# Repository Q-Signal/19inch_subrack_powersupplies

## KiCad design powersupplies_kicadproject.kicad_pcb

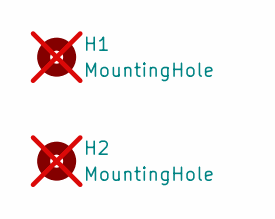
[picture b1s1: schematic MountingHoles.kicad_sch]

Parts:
H1, H2: MountingHole; MountingHole_2.7mm_M2.5; not fitted

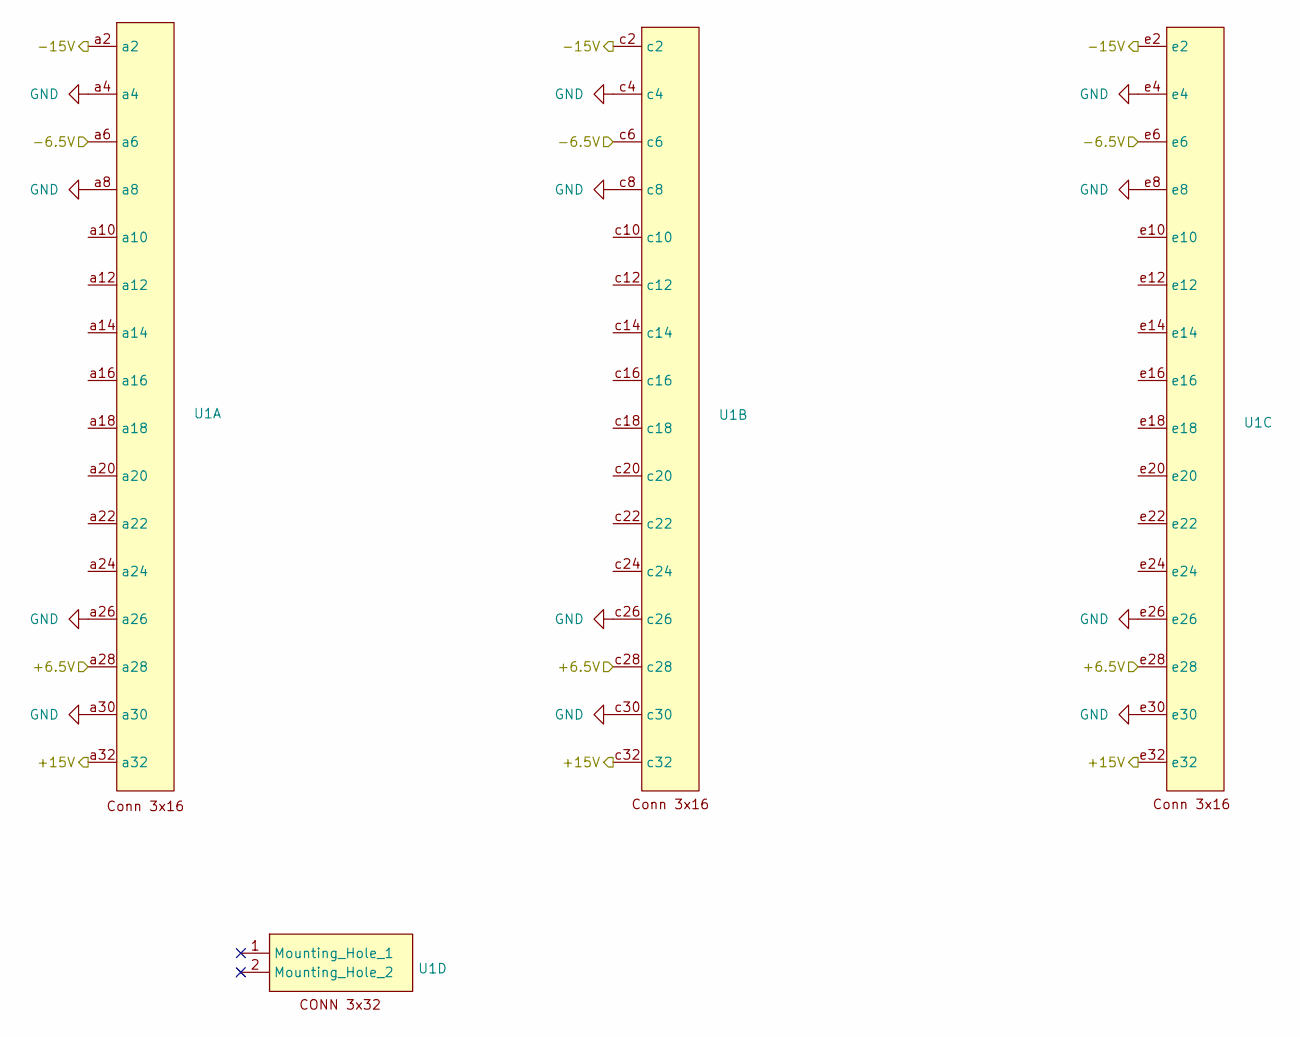
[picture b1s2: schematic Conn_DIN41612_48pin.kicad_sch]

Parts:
U1: DIN41612_ace_3x16_RA_Male; Manufacturer Part Number 09051486931; DigiKey Part Number 1195-1240-ND

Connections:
/6.5V Dual Rail Power/+6.5V: U1.a28, U1.c28, U1.e28; also elsewhere on the board
/6.5V Dual Rail Power/+15V: U1.a32, U1.c32, U1.e32; also elsewhere on the board
/6.5V Dual Rail Power/-6.5V: U1.a6, U1.c6, U1.e6; also elsewhere on the board
/6.5V Dual Rail Power/-15V: U1.a2, U1.c2, U1.e2; also elsewhere on the board
GND: U1.a4, U1.a8, U1.a26, U1.a30, U1.c4, U1.c8, U1.c26, U1.c30, U1.e4, U1.e8, U1.e26, U1.e30; also elsewhere on the board

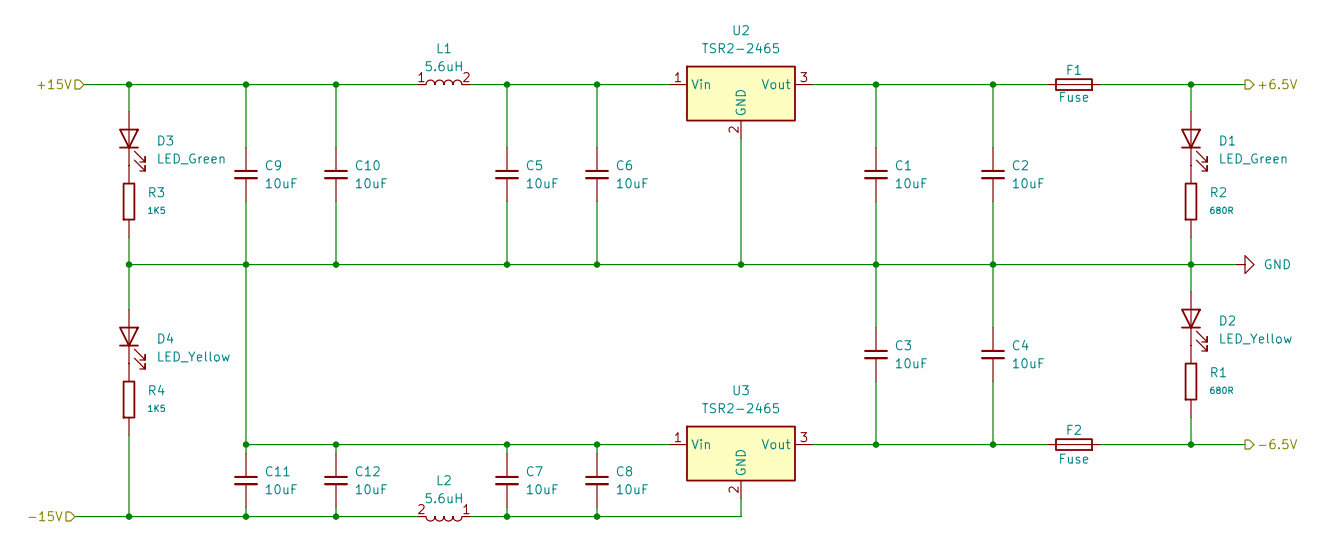
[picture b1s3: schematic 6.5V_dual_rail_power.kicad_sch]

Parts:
C1, C2, C3, C4, C5, C6, C7, C8, C9, C10, C11, C12: 10uF; C_1206_3216Metric_Pad1.33x1.80mm_HandSolder; Manufacturer Part Number GRM31CR71E106KA12L; DigiKey Part Number 490-6518-2-ND
D1, D3: LED_Green; LED_TH_RA; Manufacturer Part Number WP1503CB/GD; DigiKey Part Number 754-1555-ND
D2, D4: LED_Yellow; LED_TH_RA; Manufacturer Part Number WP1503CB/YD; DigiKey Part Number 754-1714-ND
F1, F2: Fuse; LittleFuse_01550900M; Manufacturer Part Number 01550900M; DigiKey Part Number F1889-ND
L1, L2: 5.6uH; TCK141; Manufacturer Part Number TCK-141; DigiKey Part Number 1951-1052-ND
R1, R2: 680R; R_1206_3216Metric_Pad1.30x1.75mm_HandSolder; Manufacturer Part Number RT1206FRE07680RL; DigiKey Part Number 13-RT1206FRE07680RLTR-ND
R3, R4: 1K5; R_1206_3216Metric_Pad1.30x1.75mm_HandSolder; Manufacturer Part Number RT1206BRE071K5L; DigiKey Part Number 13-RT1206BRE071K5LTR-ND
U2, U3: TSR2-2465; Converter_DCDC_TRACO_TSR2-xxxx_THT; Manufacturer Part Number TSR 2-2465; DigiKey Part Number 1951-2427-ND

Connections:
/6.5V Dual Rail Power/+6.5V: D1.2 (A), F1.2; also elsewhere on the board
/6.5V Dual Rail Power/+15V: C9.1, C10.1, D3.2 (A), L1.1; also elsewhere on the board
/6.5V Dual Rail Power/-6.5V: F2.2, R1.1; also elsewhere on the board
/6.5V Dual Rail Power/-15V: C11.2, C12.2, L2.2, R4.1; also elsewhere on the board
GND: C1.2, C2.2, C3.1, C4.1, C5.2, C6.2, C7.1, C8.1, C9.2, C10.2, C11.1, C12.1, D2.2 (A), D4.2 (A), R2.1, R3.1, U2.2 (GND), U3.1 (Vin); also elsewhere on the board
unnamed: D1.1 (K), R2.2
unnamed: D2.1 (K), R1.2
unnamed: D3.1 (K), R3.2
unnamed: D4.1 (K), R4.2
unnamed: C5.1, C6.1, L1.2, U2.1 (Vin)
unnamed: C1.1, C2.1, F1.1, U2.3 (Vout)
unnamed: C7.2, C8.2, L2.1, U3.2 (GND)
unnamed: C3.2, C4.2, F2.1, U3.3 (Vout)

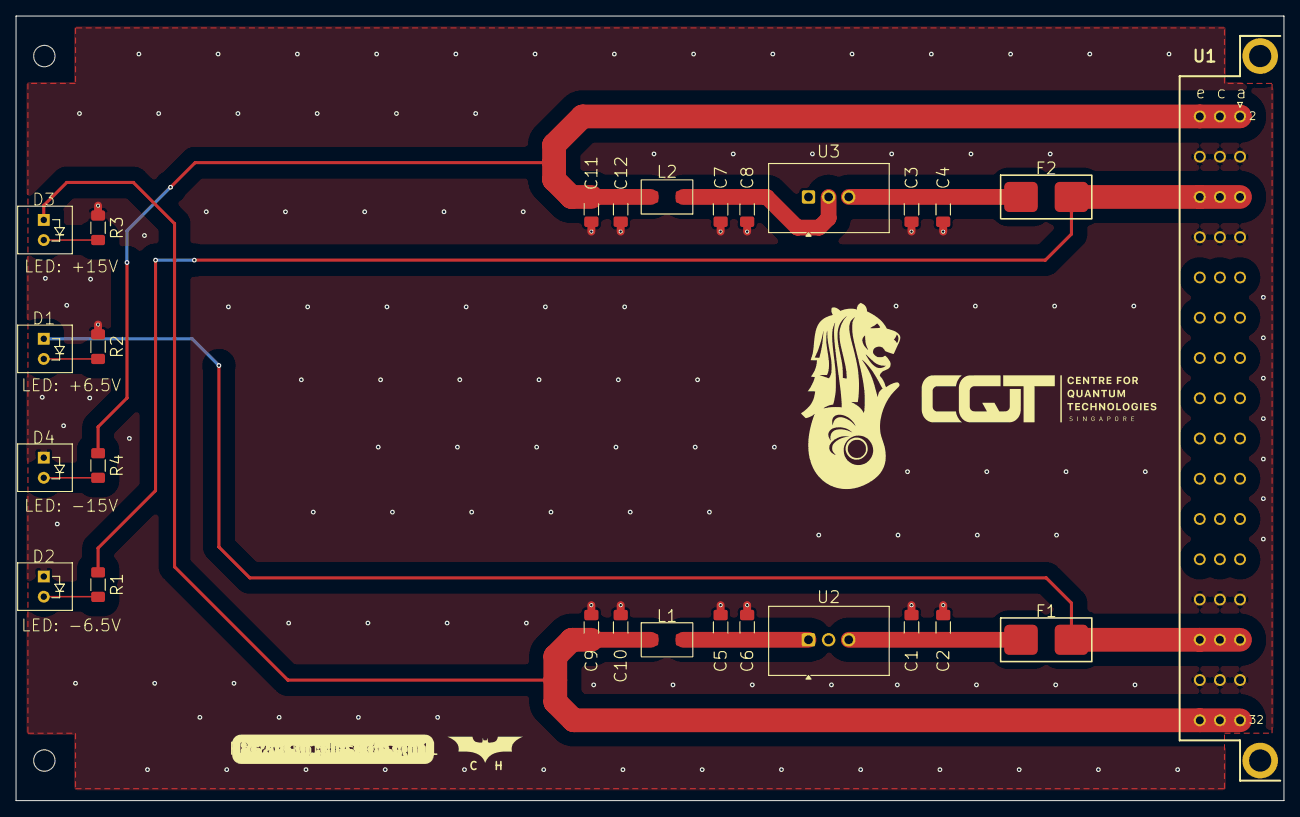
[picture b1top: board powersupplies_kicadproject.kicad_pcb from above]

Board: 2 copper layers, 160.0 x 99.0 mm, 29 parts (0 on the bottom side), 13 nets.

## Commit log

2026-06-12 Initial commit.
2026-06-12 Save progress.
2026-06-15 Exchange SMD fuse with SMD fuse holder.
2026-06-15 Added and routed power LEDs.
2026-06-16 Added fab files.
2026-06-16 Added pcb images.
